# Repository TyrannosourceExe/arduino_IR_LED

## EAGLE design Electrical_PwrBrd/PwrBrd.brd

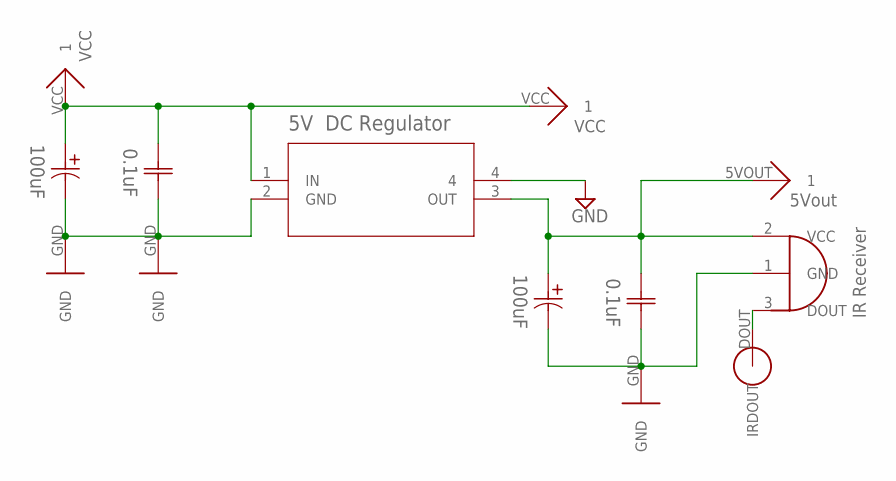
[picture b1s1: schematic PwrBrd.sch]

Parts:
C1, C2: UPW1A101MDD; PCAP_5X11-THRU-ELECT
C3, C4: UVR2A0R1MDD; U1-E
U1: MIC5239-5.0YS; SOT-223_S
U$1: IRRECV
U$2, U$3: VCC
U$4: 5VOUT
U$5: IRDOUT
U$6, U$7, U$8: GND

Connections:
GND: C1.2 (22), C2.2 (22), C3.2 (22), C4.2 (22), U1.2 (GND), U1.4, U$1.1 (GND), U$6.GND, U$7.GND, U$8.GND
unnamed: C1.1 (11), C3.1 (11), U1.1 (IN), U$2.VCC, U$3.VCC
unnamed: U$1.3 (DOUT), U$5.DOUT
unnamed: C2.1 (11), C4.1 (11), U1.3 (OUT), U$1.2 (VCC), U$4.5VOUT

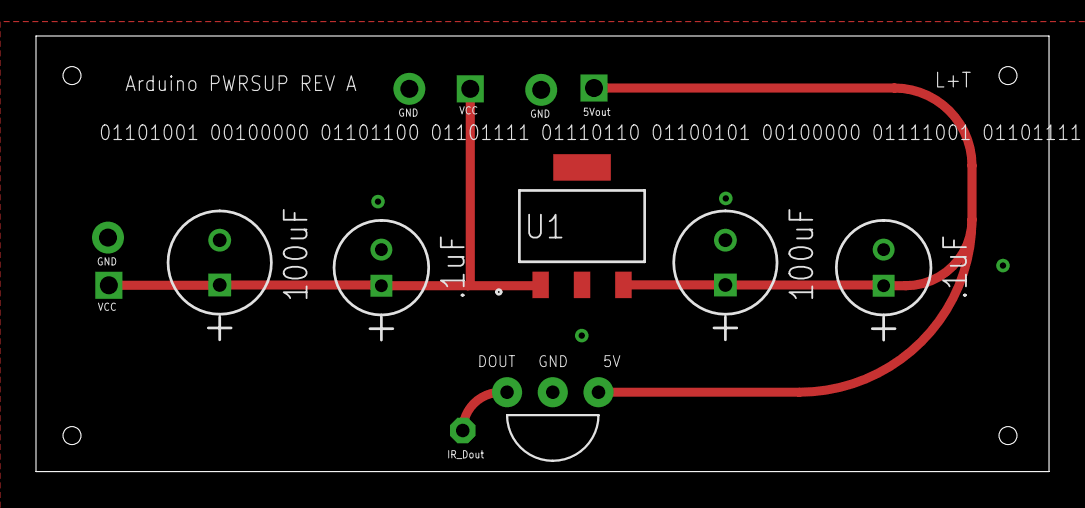
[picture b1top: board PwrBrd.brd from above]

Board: 2 copper layers, 56.3 x 24.2 mm, 13 parts (0 on the bottom side), 4 nets.

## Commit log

2018-11-28 initial upload of all power board design files
2018-11-29 added arduino code
2018-12-02 IR initial code
2018-12-14 added additional settings in the IR
2018-12-24 sync code, CAD, electrical, and drawing files
